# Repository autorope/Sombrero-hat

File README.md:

# Sombrero-hat
This is the board files for the Sombrero hat.  The Sombrero hat should just work with the most recent donkey software, however if you are hacking on it. The following Pins will matter to you:

* PMW OUT (0-5) - PCA Channel 2-7
* I2C.SDA - BCM[0]
* I2C.SCL - BCM[1]
* LED.0 - BCM[13]
* LED.2 - BCM[19]
* GPIO.0 - BCM[16]
* GPIO.1 - BCM[20]
* GPIO.2 - BCM[21]
* Enable BCM [26]

The most important one, is that the hat has an enable pin - this has to be pulled low in order for the car to work.  This is always a nice feature for all robots as it can act as a kill switch.  The LEDs need to be driven low as well in order to work.

Ths Sombrero buck converter is a 3A converter and will work with all Rasberry Pis including the pi4

For more information on the hat watch this [video](https://youtu.be/vuAXdrtNjpk)

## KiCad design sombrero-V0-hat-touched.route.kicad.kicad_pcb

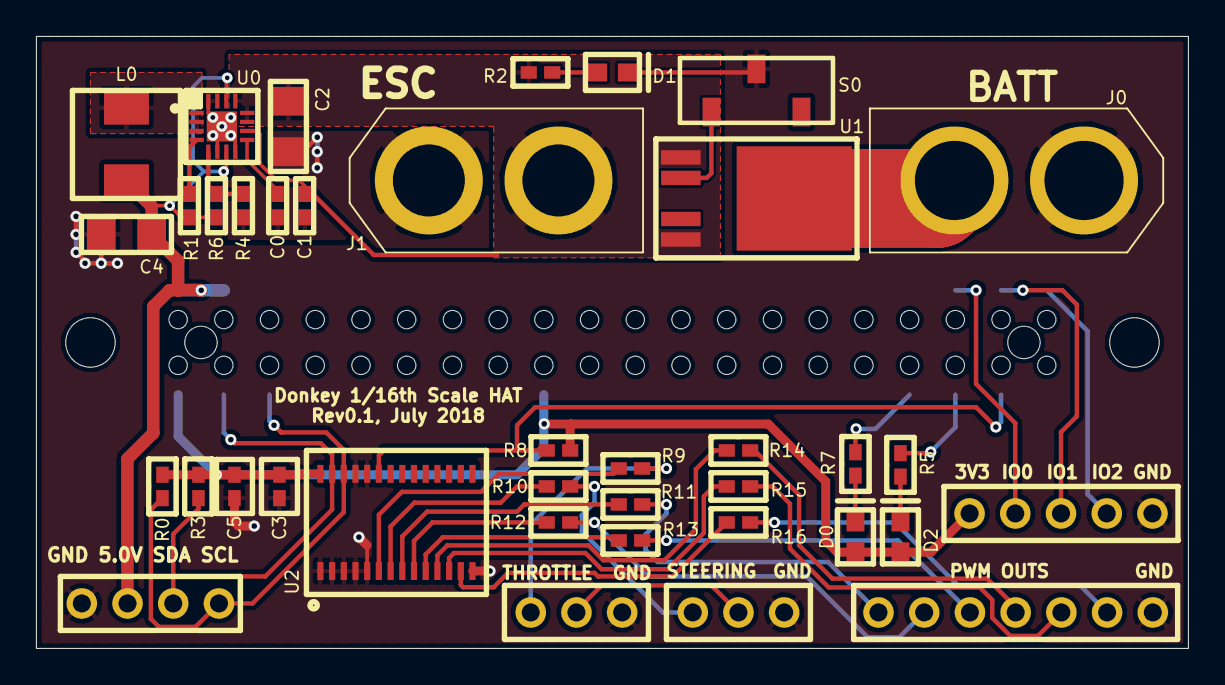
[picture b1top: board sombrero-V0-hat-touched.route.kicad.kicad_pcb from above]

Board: 2 copper layers, 64.0 x 34.0 mm, 34 parts (1 on the bottom side), 26 nets.

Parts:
C0, C1, C3, C5: CAPC1005X55
C2, C4: CAPC3216X160
D0, D1, D2: LEDSC16080X80
J0: XT-60-male-pkg
J1: XT-60-female-pkg
J7: raspi-3B+-pkg
L0: INDM560520X300
R0, R1, R2, R3, R4, R5, R6, R7, R8, R9, R10, R11, R12, R13, R14, R15, R16: RESC1005X35
S0: SW-JS102011JCQN-pkg
U0: QFN50P300X300X100-16
U1: d-pak-5-pkg
U2: SOP65P640X110-28N

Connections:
conn-XT-60-pass-0-inst_conn_noname548: S0.0, U1.1
conn-XT-60-pass-0-inst_conn_noname550: D1.0, R2.1
conn-XT-60-pass-0-inst_conn_noname552: J0.1, U1.2
dio: J7.32, R7.0
dio$2: J7.34, R5.0
gnd: C0.1, C1.1, C2.1, C3.0, C4.1, C5.0, D1.1, J0.0, J1.0, J7.5, J7.8, J7.13, J7.19, J7.24, J7.29, J7.33, J7.38, R4.1, S0.1, U0.5, U0.7, U0.14, U0.15, U0.16, U2.0, U2.1, U2.2, U2.3, U2.4, U2.13, U2.23, U2.24
led$2_noname732: D2.1, R5.1
led_noname732: D0.1, R7.1
noname764_scl: J7.4, R0.0, U2.25
noname764_sda: J7.2, R3.0, U2.26
pi_noname681: C0.0, U0.8
pi_noname682: L0.0, U0.0, U0.1, U0.2
pi_noname683: R1.1, U0.3
pi_noname684: R4.0, R6.1, U0.4
pow-3v3_pos: C3.1, C5.1, D0.0, D2.0, J7.0, J7.16, R0.1, R3.1, R8.0, U2.27
pow-5v0_pos: C4.0, J7.1, J7.3, L0.1, R1.0, R6.0, U0.6, U0.13
pow-7v4_pos: C1.0, C2.0, J1.1, R2.0, U0.9, U0.10, U0.11, U0.12, U1.0, U1.4
servo-connectors_noname564: R9.0, U2.5
servo-connectors_noname565: R10.0, U2.6
servo-connectors_noname574: R11.0, U2.7
servo-connectors_noname575: R12.0, U2.8
servo-connectors_noname576: R13.0, U2.9
servo-connectors_noname577: R14.0, U2.10
servo-connectors_noname578: R15.0, U2.11
servo-connectors_noname579: R16.0, U2.12
servo-connectors_pwm-drv_noname594: J7.36, R8.1, U2.22

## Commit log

2019-02-24 Upload Kicad files.
2019-03-01 Create LICENSE
